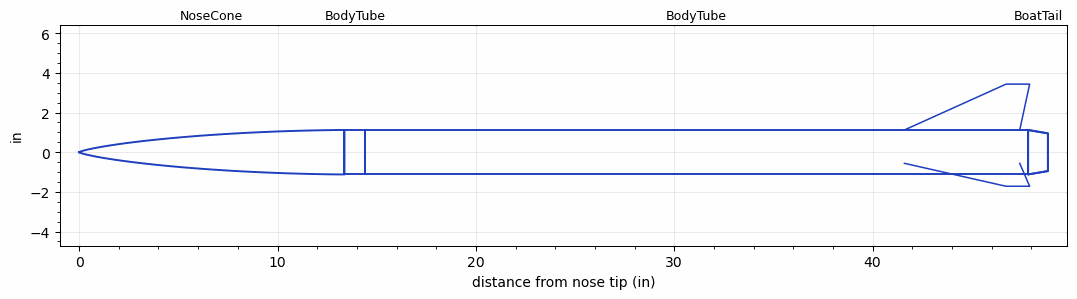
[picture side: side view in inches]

<RASAeroDocument>
 <FileVersion>2</FileVersion>
 <RocketDesign>
  <NoseCone>
   <Length>13.375</Length>
   <Diameter>2.241</Diameter>
   <Shape>LV-Haack</Shape>
   <Location>0</Location>
  </NoseCone>
  <BodyTube>
   <Length>1.0415</Length>
   <Diameter>2.241</Diameter>
   <Location>13.375</Location>
  </BodyTube>
  <BodyTube>
   <Length>33.42</Length>
   <Diameter>2.241</Diameter>
   <Location>14.4165</Location>
   <BoattailLength>1</BoattailLength>
   <BoattailRearDiameter>1.9</BoattailRearDiameter>
   <Fin>
    <Count>3</Count>
    <Chord>5.813</Chord>
    <Span>2.313</Span>
    <SweepDistance>5.125</SweepDistance>
    <TipChord>1.188</TipChord>
    <Thickness>0.124</Thickness>
    <Location>6.233</Location>
    <AirfoilSection>Hexagonal Blunt Base</AirfoilSection>
    <FX1>0.5</FX1>
   </Fin>
  </BodyTube>
  <BoatTail>
   <Length>1</Length>
   <Diameter>2.241</Diameter>
   <RearDiameter>1.9</RearDiameter>
   <Location>47.8365</Location>
  </BoatTail>
  <Surface>Smooth Paint</Surface>
  <ModifiedBarrowman>True</ModifiedBarrowman>
  <Turbulence>False</Turbulence>
  <UseBooster1>False</UseBooster1>
  <UseBooster2>False</UseBooster2>
 </RocketDesign>
 <LaunchSite>
  <Altitude>1250</Altitude>
  <Pressure>0</Pressure>
  <RodAngle>0</RodAngle>
  <RodLength>6</RodLength>
  <Temperature>90</Temperature>
  <WindSpeed>10</WindSpeed>
 </LaunchSite>
 <Recovery>
  <Altitude1>1000</Altitude1>
  <Altitude2>500</Altitude2>
  <DeviceType1>Parachute</DeviceType1>
  <DeviceType2>Parachute</DeviceType2>
  <Event1>True</Event1>
  <Event2>True</Event2>
  <Size1>6</Size1>
  <Size2>36</Size2>
  <EventType1>Apogee</EventType1>
  <EventType2>Altitude</EventType2>
  <CD1>0.5</CD1>
  <CD2>0.98</CD2>
 </Recovery>
 <SimulationList>
  <Simulation>
   <SustainerEngine>K590  (CTI)</SustainerEngine>
   <SustainerLaunchWt>6.63</SustainerLaunchWt>
   <SustainerCG>32.84</SustainerCG>
   <SustainerIgnitionDelay>0</SustainerIgnitionDelay>
   <Booster1SeparationDelay>0</Booster1SeparationDelay>
   <Booster1IgnitionDelay>0</Booster1IgnitionDelay>
   <IncludeBooster1>False</IncludeBooster1>
   <Booster2Delay>0</Booster2Delay>
   <IncludeBooster2>False</IncludeBooster2>
   <TimetoApogee>31.53063</TimetoApogee>
   <MaxAltitude>23593.61</MaxAltitude>
   <MaxVelocity>2257.082</MaxVelocity>
  </Simulation>
  <Simulation>
   <SustainerEngine>K660  (CTI)</SustainerEngine>
   <SustainerLaunchWt>6.94</SustainerLaunchWt>
   <SustainerCG>30.94</SustainerCG>
   <SustainerIgnitionDelay>0</SustainerIgnitionDelay>
   <Booster1SeparationDelay>0</Booster1SeparationDelay>
   <Booster1IgnitionDelay>0</Booster1IgnitionDelay>
   <IncludeBooster1>False</IncludeBooster1>
   <Booster2Delay>0</Booster2Delay>
   <IncludeBooster2>False</IncludeBooster2>
   <TimetoApogee>31.74063</TimetoApogee>
   <MaxAltitude>23333.61</MaxAltitude>
   <MaxVelocity>2343.251</MaxVelocity>
  </Simulation>
  <Simulation>
   <SustainerEngine>J380SS  (CTI)</SustainerEngine>
   <SustainerLaunchWt>5.23</SustainerLaunchWt>
   <SustainerCG>33.03</SustainerCG>
   <SustainerIgnitionDelay>0</SustainerIgnitionDelay>
   <Booster1SeparationDelay>0</Booster1SeparationDelay>
   <Booster1IgnitionDelay>0</Booster1IgnitionDelay>
   <IncludeBooster1>False</IncludeBooster1>
   <Booster2Delay>0</Booster2Delay>
   <IncludeBooster2>False</IncludeBooster2>
   <TimetoApogee>24.03045</TimetoApogee>
   <MaxAltitude>11715.26</MaxAltitude>
   <MaxVelocity>1424.447</MaxVelocity>
  </Simulation>
  <Simulation>
   <SustainerEngine>K260-CL  (CTI)</SustainerEngine>
   <SustainerLaunchWt>7.19</SustainerLaunchWt>
   <SustainerCG>31.1</SustainerCG>
   <SustainerIgnitionDelay>0</SustainerIgnitionDelay>
   <Booster1SeparationDelay>0</Booster1SeparationDelay>
   <Booster1IgnitionDelay>0</Booster1IgnitionDelay>
   <IncludeBooster1>False</IncludeBooster1>
   <Booster2Delay>0</Booster2Delay>
   <IncludeBooster2>False</IncludeBooster2>
   <TimetoApogee>33.87032</TimetoApogee>
   <MaxAltitude>22977.56</MaxAltitude>
   <MaxVelocity>1670.348</MaxVelocity>
  </Simulation>
  <Simulation>
   <SustainerEngine>K820-BS  (CTI)</SustainerEngine>
   <SustainerLaunchWt>6.56</SustainerLaunchWt>
   <SustainerCG>32.83</SustainerCG>
   <SustainerIgnitionDelay>0</SustainerIgnitionDelay>
   <Booster1SeparationDelay>0</Booster1SeparationDelay>
   <Booster1IgnitionDelay>0</Booster1IgnitionDelay>
   <IncludeBooster1>False</IncludeBooster1>
   <Booster2Delay>0</Booster2Delay>
   <IncludeBooster2>False</IncludeBooster2>
   <TimetoApogee>30.13059</TimetoApogee>
   <MaxAltitude>22247.24</MaxAltitude>
   <MaxVelocity>2576.449</MaxVelocity>
  </Simulation>
  <Simulation>
   <SustainerEngine>K1440  (CTI)</SustainerEngine>
   <SustainerLaunchWt>6.38</SustainerLaunchWt>
   <SustainerCG>32.72</SustainerCG>
   <SustainerIgnitionDelay>0</SustainerIgnitionDelay>
   <Booster1SeparationDelay>0</Booster1SeparationDelay>
   <Booster1IgnitionDelay>0</Booster1IgnitionDelay>
   <IncludeBooster1>False</IncludeBooster1>
   <Booster2Delay>0</Booster2Delay>
   <IncludeBooster2>False</IncludeBooster2>
   <TimetoApogee>29.24057</TimetoApogee>
   <MaxAltitude>21701.15</MaxAltitude>
   <MaxVelocity>2890.69</MaxVelocity>
  </Simulation>
 </SimulationList>
</RASAeroDocument>
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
